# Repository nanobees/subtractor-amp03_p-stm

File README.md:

# subtractor-amp03_p-stm
A Low Noise Subtractor Circuit for Photon-Scanning Tunneling Microscope System

This easy circuit is crucial part of our photon scanning tunneling microscope system. It helps us to convert the signals
that comes from a Nanosurf Easy Scan STM to NanoMagnetics Instruments Electronics.
For further information please contact with me: haltugyildirim_at_protonmail.com

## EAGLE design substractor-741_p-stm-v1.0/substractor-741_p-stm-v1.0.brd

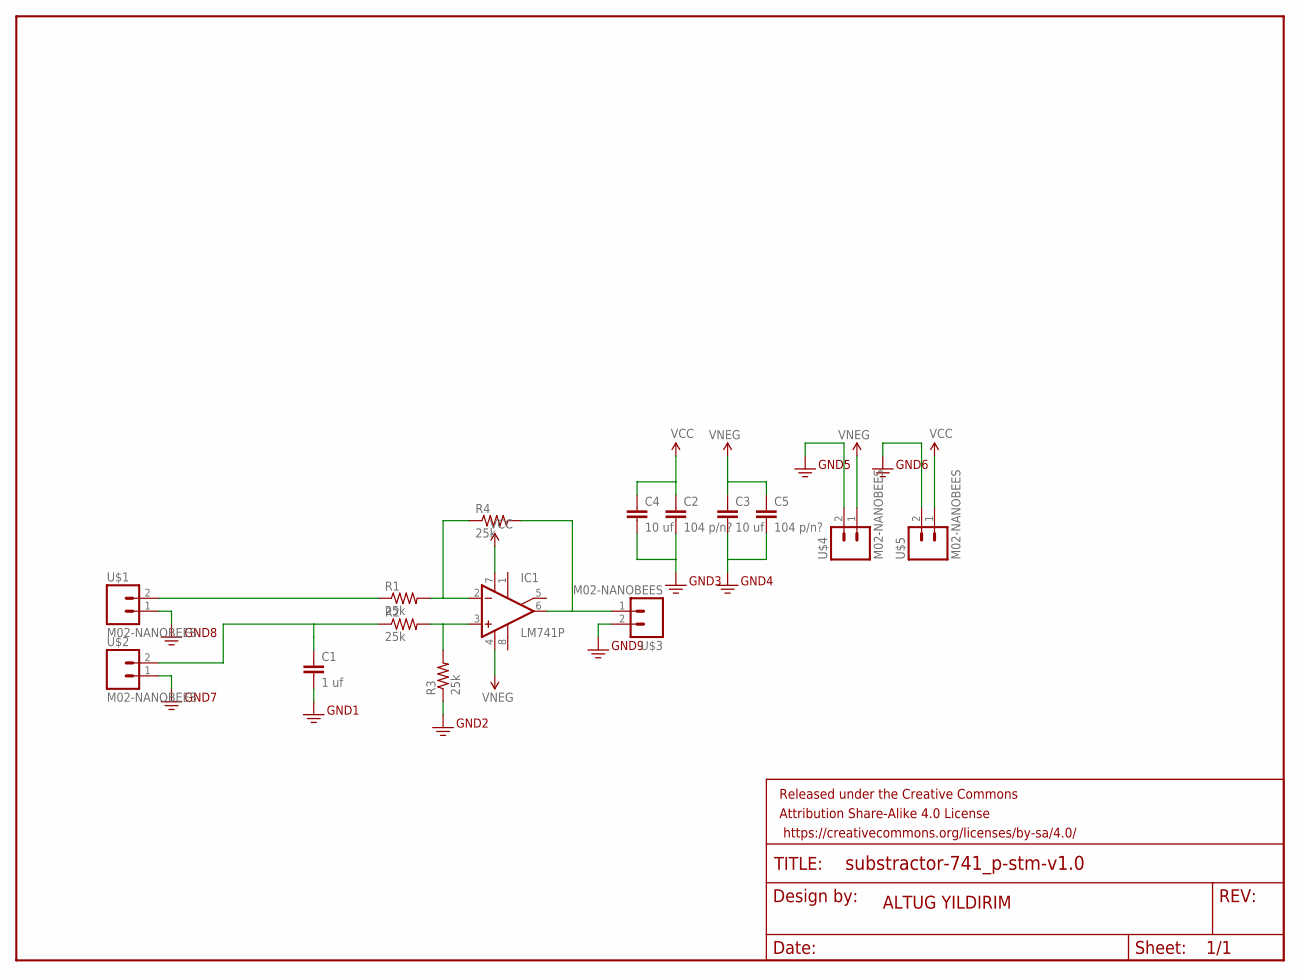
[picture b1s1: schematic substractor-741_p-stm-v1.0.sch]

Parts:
C1: 1 uf; CAP-PTH-SMALL2
C2, C5: 104 p/n?; CAP-PTH-SMALL2
C3, C4: 10 uf; CAP-PTH-SMALL2
FRAME1: FRAME-LETTER; CREATIVE_COMMONS
IC1: LM741P; DIL08
R1, R2, R3, R4: 25k; AXIAL-0.4
U$1, U$2, U$3, U$4, U$5: M02-NANOBEES

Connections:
GND: C1.2, C2.2, C3.2, C4.2, C5.2, R3.P$1 (1), U$1.1, U$2.1, U$3.2, U$4.2, U$5.2
unnamed: R1.P$1 (1), U$1.2
unnamed: C1.1, R2.P$1 (1), U$2.2
unnamed: IC1.2 (+IN), R1.P$2 (2), R4.P$1 (1)
unnamed: IC1.3 (-IN), R2.P$2 (2), R3.P$2 (2)
unnamed: IC1.6 (OUT), R4.P$2 (2), U$3.1
VCC: C2.1, C4.1, IC1.7 (V+), U$5.1
VNEG: C3.1, C5.1, IC1.4 (V-), U$4.1

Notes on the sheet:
ALTUG YILDIRIM

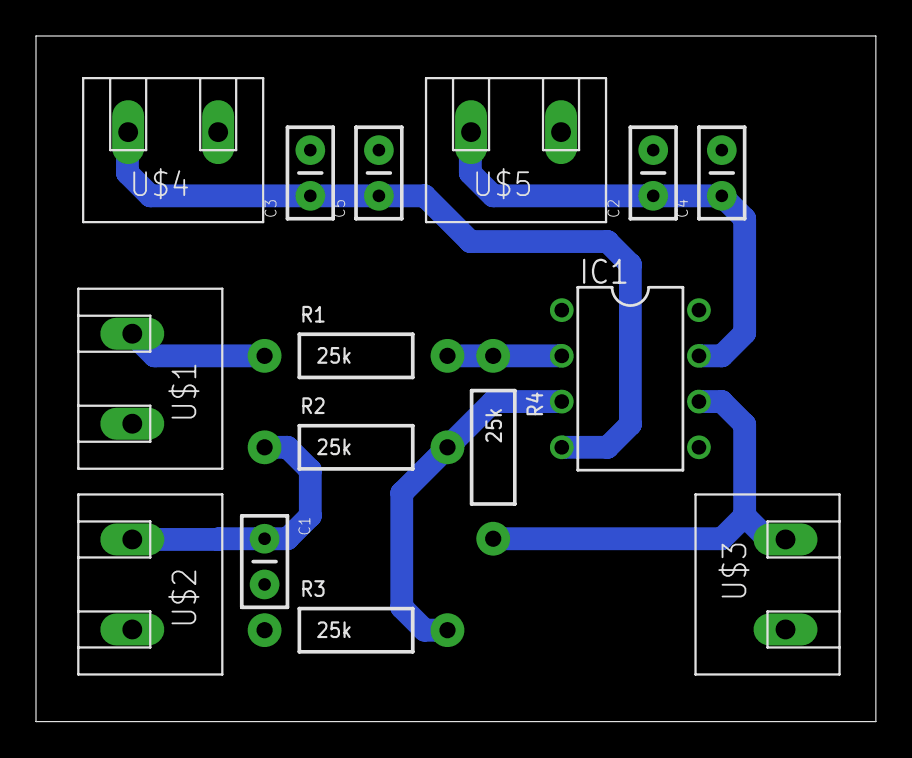
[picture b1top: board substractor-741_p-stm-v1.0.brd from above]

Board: 2 copper layers, 46.7 x 38.1 mm, 16 parts (0 on the bottom side), 8 nets.

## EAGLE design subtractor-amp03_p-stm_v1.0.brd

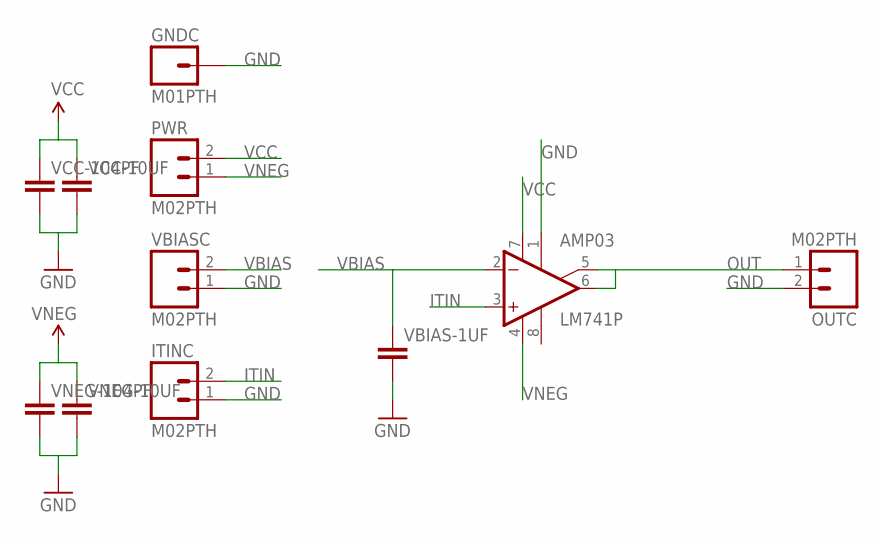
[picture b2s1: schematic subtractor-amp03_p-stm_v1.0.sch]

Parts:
AMP03: LM741P; DIL08
GNDC: M01PTH; 1X01
ITINC: M02PTH; 1X02
OUTC: M02PTH; 1X02
PWR: M02PTH; 1X02
VBIAS-1UF: CAPPTH2; CAP-PTH-SMALL2
VBIASC: M02PTH; 1X02
VCC-10UF, VCC-104PF: CAPPTH2; CAP-PTH-SMALL2
VNEG-10UF, VNEG-104PF: CAPPTH2; CAP-PTH-SMALL2

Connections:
GND: AMP03.1 (ON1), GNDC.1, ITINC.1, OUTC.2, VBIAS-1UF.2, VBIASC.1, VCC-10UF.2, VCC-104PF.2, VNEG-10UF.2, VNEG-104PF.2
ITIN: AMP03.3 (-IN), ITINC.2
OUT: AMP03.5 (ON2), AMP03.6 (OUT), OUTC.1
VBIAS: AMP03.2 (+IN), VBIAS-1UF.1, VBIASC.2
VCC: AMP03.7 (V+), PWR.2, VCC-10UF.1, VCC-104PF.1
VNEG: AMP03.4 (V-), PWR.1, VNEG-10UF.1, VNEG-104PF.1

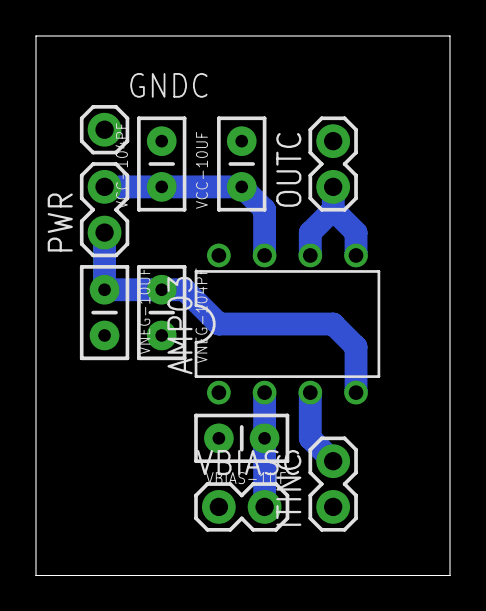
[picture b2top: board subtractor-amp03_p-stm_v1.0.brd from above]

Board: 2 copper layers, 23.0 x 30.0 mm, 11 parts (0 on the bottom side), 6 nets.

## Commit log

2016-08-26 initial design
    adding initial files
2016-08-26 adding 741 based subtractor designs
2016-08-27 adding finished product jpeg

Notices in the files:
parts and their libraries:
SparkFun-Resistors: Licensing: Creative Commons ShareAlike 4.0 International - https://creativecommons.org/licenses/by-sa/4.0
SparkFun-Aesthetics: Released under the Creative Commons Attribution Share-Alike 4.0 License
SparkFun-Aesthetics: https://creativecommons.org/licenses/by-sa/4.0
